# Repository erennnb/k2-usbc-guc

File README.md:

# K2 — USB-C 3.3 V Güç Kartı

USB-C'den aldığı 5 V'u korumalı biçimde 3.3 V'a düşüren, iki katmanlı küçük bir güç kartı.
Yol haritamdaki ilk "üretime hazır" kart: şema, PCB, üretim dosyaları ve doğrulama bu repoda.

> **Durum:** Tasarım tamamlandı · DRC temiz · Gerber hazır · Sipariş verilmedi (simülasyon + inceleme ile doğrulanıyor)

---

## Özellikler

| | |
|---|---|
| **Giriş** | USB-C, yalnız güç (6 pin), 5 V |
| **Çıkış** | 3.3 V, en az 500 mA · ayrıca 5 V çıkış |
| **Koruma** | Polyfuse (aşırı akım) + TVS diyot (gerilim darbesi, ESD) |
| **Gösterge** | 3.3 V hattında güç LED'i |
| **Bağlantı** | 1×3 pin header (5V, 3V3, GND) + 3 test noktası |
| **Kart** | 2 katman, 51.5 × 16 mm |

## Blok diyagram

```mermaid
flowchart LR
    A["USB-C<br/>5 V"] --> B["Polyfuse<br/>0.75 A"]
    B --> C["TVS<br/>SMAJ6.0A"]
    C --> D["AMS1117-3.3<br/>LDO"]
    D --> E["3.3 V çıkış<br/>J2 · TP2"]
    C --> F["5 V çıkış<br/>J2 · TP1"]
    D --> G["Güç LED'i"]
    A -. "CC1 / CC2" .-> H["2 × 5.1 kΩ<br/>pull-down"]
```

## Şema

[Şemanın PDF hâli](docs/k2-schematic.pdf)

## PCB

| Üst yüz | Alt yüz |
|---|---|
|  |  |

---

## Malzeme listesi (BOM)

| Ref | Parça | LCSC | JLCPCB | Not |
|---|---|---|---|---|
| J1 | SHOU HAN TYPE-C 6P | C456012 | Extended | Yalnız güç, SMD, dik açılı, THT tırnaklı |
| R1, R2 | 5.1 kΩ %1 0805 | C27834 | Basic | CC1 / CC2 pull-down |
| F1 | FSMD075-1206R | C5144563 | Extended | Polyfuse, I_hold 0.75 A, V_max 8 V |
| D1 | SMAJ6.0A | C83329 | Extended | TVS, tek yönlü, V_R 6.0 V, V_C 10.3 V |
| C1 | 10 µF 25 V X5R 0805 | C15850 | Basic | LDO giriş kondansatörü |
| U1 | AMS1117-3.3 (SOT-223) | C6186 | Basic | 3.3 V LDO |
| C2 | 22 µF 10 V tantal (B kılıf) | C7198 | Extended | LDO çıkış kondansatörü, ESR 2.4 Ω |
| D2 | Kırmızı LED 0805 | C84256 | Basic | V_F 1.6–2.6 V |
| R3 | 1 kΩ %1 0805 | C17513 | Basic | LED akım direnci |
| J2 | 1×3 pin header, 2.54 mm | — | — | Dik, THT |
| TP1–TP3 | Test noktası | — | — | PCB pad'i |

---

## Tasarım kararları ve hesaplar

### Regülatör: neden AMS1117, neden AP2112K değil?

5 V → 3.3 V, 500 mA'de regülatörde harcanan güç:

**P = (5 − 3.3) × 0.5 = 0.85 W**

| | AMS1117-3.3 (SOT-223) | AP2112K-3.3 (SOT-23-5) |
|---|---|---|
| Dropout (maks.) | 1.3 V | 0.4 V |
| θJA | 90 °C/W | 184 °C/W |
| ΔT (0.85 W) | ≈ 77 °C | ≈ 156 °C |
| Tj (25 °C ortam) | ≈ 102 °C ✓ | ≈ 181 °C ✗ |

AP2112K dropout'ta çok daha iyi, ama küçük kılıfı 0.85 W'ı atamıyor: 25 °C ortamda en fazla ~320 mA verebilir.
500 mA gereksinimi için **AMS1117** seçildi. Bedeli: dropout payı az ve termal bakır alan şart.

### Termal hesap: Tj = Ta + P × θJA

| Ortam (Ta) | Tj | 125 °C sınırı |
|---|---|---|
| 25 °C | 101,5 °C | 125 °C sınırının altında |
| 40 °C | 116,5 °C | Sınıra yakın, pay az |
| 60 °C | 136,5 °C | 125 °C’yi aşıyor |

<!-- TODO: Hangi sıcaklıkta sınır aşılıyor, o durumda ne yapılmalı? -->

### Koruma

- **Polyfuse (0.75 A):** I_hold, 500 mA'lik yük akımının üstünde olmalı; sıcaklıkla düşen I_hold ve açılıştaki ani akımlar için ~%50 pay bırakıldı. V_max 8 V, darbe sırasında hattın kısa süre 5 V'u aşmasına karşı pay.
- **TVS (SMAJ6.0A):** USB-C'de VBUS 5.5 V'a kadar çıkabildiği için V_R ≥ 5.5 V olmalı → 5.0A yerine 6.0A. V_C = 10.3 V, AMS1117'nin maksimum giriş geriliminin altında. Hat hiç negatife düşmediği için **tek yönlü**; negatif darbeleri de ~−0.7 V'ta keser.

### Kondansatörler

- **C1 = 10 µF seramik:** AMS1117 datasheet'inin önerdiği değer. USB, cihazın VBUS hattındaki kapasiteyi 10 µF ile sınırlar (açılıştaki ani akım için). 25 V değer, DC bias kaybını azaltmak için.
- **C2 = 22 µF tantal:** AMS1117 kararlı çalışmak için çıkış kondansatöründe belirli bir ESR ister; çok düşük ESR'li seramik kondansatörle salınıma girebilir.

### CC dirençleri

<!-- TODO: 2–3 cümleyle kendi cümlelerinle yaz:
     1) Bu dirençler ne işe yarıyor?
     2) İkisini neden tek dirençle birleştiremeyiz?
     3) Hiç direnç koymazsan ne olur? -->

### Güç LED'i

R = (3.3 − V_F) / I → (3.3 − 2.0) / 1 kΩ ≈ **1.3 mA**.
Yeşil LED'in V_F değeri (2.6–3.1 V) 3.3 V'a çok yakın olduğu için kırmızı seçildi.

### PCB yerleşimi

- **İz genişlikleri:** güç hatları 0.5 mm (500 mA'de 30 mm'lik izde ≈ 15 mV düşüm), sinyal hatları 0.25 mm.
- **Alt katman kesintisiz GND düzlemi.** SMD GND pad'leri kendi via'larıyla düzleme iner.
- **USB-C'nin iki VBUS pad'i** (A9, B9) arada CC pad'leri olduğu için alt katmanda kısa bir izle birleştirildi.
- **TVS'nin GND via'sı** pad'in dibinde: darbe akımı en kısa yoldan düzleme gitsin.
- **AMS1117'nin tab'ı** (+3V3) üst katmanda katı bağlantılı bir bakır alana bağlı: termal soğutucu.
- **USB-C** kart kenarından taşacak şekilde yerleştirildi; fiş tam otursun.

---

## Doğrulama

| Kontrol | Sonuç |
|---|---|
| ERC (şema) | 0 hata |
| DRC (PCB) | 0 hata, 0 uyarı |
| Şema ↔ PCB paritesi | 0 fark |
| Bağlantısız öğe | 0 |
| İstisnalar | 2 — J1'in silkscreen'i kart kenarında kırpılıyor (konnektör bilerek kenardan taşıyor) |
| JLCPCB önizlemesi | 2 katman, 16 × 51.5 mm, sorun yok |

### LTspice: yük basamağı (0 → 500 mA)

Yük basamağında çıkış kısa süreliğine 2,8 V’a düşüyor, 3,7 V’a fırlıyor ve yaklaşık 10 µs içinde 3,3 V’a oturuyor.

<!-- TODO: Çıkış ne kadar düştü, ne kadar sürede toparlandı? (Model: LT1117-3.3) -->

---

## Üretim

- Gerber + delik dosyaları: [`gerber.zip`](gerber.zip)
- JLCPCB önizlemesi: 2 katman, 51.5 × 16 mm
- Tahmini maliyet (5 adet, 17 Kasım 2026): kart $4.10 + kargo ≈ $26

---

## Öğrendiklerim

- **Özet bilgiler çelişebilir, geçerli olan datasheet.** USB-C konnektörü için JLCPCB 3 A, LCSC 5 A diyordu.
- **Çok versiyonlu datasheet'lerde doğru tabloya bak.** AP2112K'nın dropout'unu ilk okumada 2.5 V'luk versiyonun tablosundan okudum.
- **3.3 V'ta yeşil, mavi ve beyaz LED sorunlu**: V_F'leri 3 V civarında.
- **İndirilen footprint'lerde pad numaralarını sembolle karşılaştır.** EasyEDA kılıf tırnaklarına `7` demişti, KiCad sembolü `SH` bekliyordu.
- **3D görünüm hata yakalar.** İndirilen 3D model 180° ters ve kaymıştı; footprint ise doğruydu.
- **AI'ın verdiği pin numarasını doğrula.** Kılıf pininin numarası bana `S1` olarak söylendi, gerçekte `SH`'ydi; KiCad'in hata mesajı yakaladı.

## v2 için notlar

- [ ] U1'i 180° döndür: küçük pinler girişe, tab çıkışa baksın. +5V ve +3V3 hatları U1'in etrafından dolaşmasın.
- [ ] Montaj delikleri ekle.
- [ ] Termal alanı büyüt; alt katmana termal via'lı bir +3V3 adacığı düşün.
- [ ] Daha düşük dropout'lu ve 500 mA'i kaldıran bir LDO araştır.

---

## Repo yapısı

```
k2-usbc-guc/
├── k2-usbc-guc.kicad_pro / .kicad_sch / .kicad_pcb
├── lib/            USB-C footprint, sembol ve 3D model (easyeda2kicad, C456012)
├── fp-lib-table    proje footprint kütüphanesi
├── gerber/         üretim dosyaları
├── gerber.zip
└── docs/           görseller, şema PDF'i
```

KiCad 10 ile tasarlandı.# K2 — USB-C 3.3 V Güç Kartı

USB-C'den aldığı 5 V'u korumalı biçimde 3.3 V'a düşüren, iki katmanlı küçük bir güç kartı.
Yol haritamdaki ilk "üretime hazır" kart: şema, PCB, üretim dosyaları ve doğrulama bu repoda.

> **Durum:** Tasarım tamamlandı · DRC temiz · Gerber hazır · Sipariş verilmedi (simülasyon + inceleme ile doğrulanıyor)

---

## Özellikler

| | |
|---|---|
| **Giriş** | USB-C, yalnız güç (6 pin), 5 V |
| **Çıkış** | 3.3 V, en az 500 mA · ayrıca 5 V çıkış |
| **Koruma** | Polyfuse (aşırı akım) + TVS diyot (gerilim darbesi, ESD) |
| **Gösterge** | 3.3 V hattında güç LED'i |
| **Bağlantı** | 1×3 pin header (5V, 3V3, GND) + 3 test noktası |
| **Kart** | 2 katman, 51.5 × 16 mm |

## Blok diyagram

```mermaid
flowchart LR
    A["USB-C<br/>5 V"] --> B["Polyfuse<br/>0.75 A"]
    B --> C["TVS<br/>SMAJ6.0A"]
    C --> D["AMS1117-3.3<br/>LDO"]
    D --> E["3.3 V çıkış<br/>J2 · TP2"]
    C --> F["5 V çıkış<br/>J2 · TP1"]
    D --> G["Güç LED'i"]
    A -. "CC1 / CC2" .-> H["2 × 5.1 kΩ<br/>pull-down"]
```

## Şema

[Şemanın PDF hâli](docs/k2-schematic.pdf)

## PCB

| Üst yüz | Alt yüz |
|---|---|
|  |  |

---

## Malzeme listesi (BOM)

| Ref | Parça | LCSC | JLCPCB | Not |
|---|---|---|---|---|
| J1 | SHOU HAN TYPE-C 6P | C456012 | Extended | Yalnız güç, SMD, dik açılı, THT tırnaklı |
| R1, R2 | 5.1 kΩ %1 0805 | C27834 | Basic | CC1 / CC2 pull-down |
| F1 | FSMD075-1206R | C5144563 | Extended | Polyfuse, I_hold 0.75 A, V_max 8 V |
| D1 | SMAJ6.0A | C83329 | Extended | TVS, tek yönlü, V_R 6.0 V, V_C 10.3 V |
| C1 | 10 µF 25 V X5R 0805 | C15850 | Basic | LDO giriş kondansatörü |
| U1 | AMS1117-3.3 (SOT-223) | C6186 | Basic | 3.3 V LDO |
| C2 | 22 µF 10 V tantal (B kılıf) | C7198 | Extended | LDO çıkış kondansatörü, ESR 2.4 Ω |
| D2 | Kırmızı LED 0805 | C84256 | Basic | V_F 1.6–2.6 V |
| R3 | 1 kΩ %1 0805 | C17513 | Basic | LED akım direnci |
| J2 | 1×3 pin header, 2.54 mm | — | — | Dik, THT |
| TP1–TP3 | Test noktası | — | — | PCB pad'i |

---

## Tasarım kararları ve hesaplar

### Regülatör: neden AMS1117, neden AP2112K değil?

5 V → 3.3 V, 500 mA'de regülatörde harcanan güç:

**P = (5 − 3.3) × 0.5 = 0.85 W**

| | AMS1117-3.3 (SOT-223) | AP2112K-3.3 (SOT-23-5) |
|---|---|---|
| Dropout (maks.) | 1.3 V | 0.4 V |
| θJA | 90 °C/W | 184 °C/W |
| ΔT (0.85 W) | ≈ 77 °C | ≈ 156 °C |
| Tj (25 °C ortam) | ≈ 102 °C ✓ | ≈ 181 °C ✗ |

AP2112K dropout'ta çok daha iyi, ama küçük kılıfı 0.85 W'ı atamıyor: 25 °C ortamda en fazla ~320 mA verebilir.
500 mA gereksinimi için **AMS1117** seçildi. Bedeli: dropout payı az ve termal bakır alan şart.

### Termal hesap: Tj = Ta + P × θJA

| Ortam (Ta) | Tj | 125 °C sınırı |
|---|---|---|
| 25 °C | <!-- TODO --> | <!-- TODO --> |
| 40 °C | <!-- TODO --> | <!-- TODO --> |
| 60 °C | <!-- TODO --> | <!-- TODO --> |

<!-- TODO: Hangi sıcaklıkta sınır aşılıyor, o durumda ne yapılmalı? -->

### Koruma

- **Polyfuse (0.75 A):** I_hold, 500 mA'lik yük akımının üstünde olmalı; sıcaklıkla düşen I_hold ve açılıştaki ani akımlar için ~%50 pay bırakıldı. V_max 8 V, darbe sırasında hattın kısa süre 5 V'u aşmasına karşı pay.
- **TVS (SMAJ6.0A):** USB-C'de VBUS 5.5 V'a kadar çıkabildiği için V_R ≥ 5.5 V olmalı → 5.0A yerine 6.0A. V_C = 10.3 V, AMS1117'nin maksimum giriş geriliminin altında. Hat hiç negatife düşmediği için **tek yönlü**; negatif darbeleri de ~−0.7 V'ta keser.

### Kondansatörler

- **C1 = 10 µF seramik:** AMS1117 datasheet'inin önerdiği değer. USB, cihazın VBUS hattındaki kapasiteyi 10 µF ile sınırlar (açılıştaki ani akım için). 25 V değer, DC bias kaybını azaltmak için.
- **C2 = 22 µF tantal:** AMS1117 kararlı çalışmak için çıkış kondansatöründe belirli bir ESR ister; çok düşük ESR'li seramik kondansatörle salınıma girebilir.

### CC dirençleri

<!-- TODO: 2–3 cümleyle kendi cümlelerinle yaz:
     1) Bu dirençler ne işe yarıyor?
     2) İkisini neden tek dirençle birleştiremeyiz?
     3) Hiç direnç koymazsan ne olur? -->

### Güç LED'i

R = (3.3 − V_F) / I → (3.3 − 2.0) / 1 kΩ ≈ **1.3 mA**.
Yeşil LED'in V_F değeri (2.6–3.1 V) 3.3 V'a çok yakın olduğu için kırmızı seçildi.

### PCB yerleşimi

- **İz genişlikleri:** güç hatları 0.5 mm (500 mA'de 30 mm'lik izde ≈ 15 mV düşüm), sinyal hatları 0.25 mm.
- **Alt katman kesintisiz GND düzlemi.** SMD GND pad'leri kendi via'larıyla düzleme iner.
- **USB-C'nin iki VBUS pad'i** (A9, B9) arada CC pad'leri olduğu için alt katmanda kısa bir izle birleştirildi.
- **TVS'nin GND via'sı** pad'in dibinde: darbe akımı en kısa yoldan düzleme gitsin.
- **AMS1117'nin tab'ı** (+3V3) üst katmanda katı bağlantılı bir bakır alana bağlı: termal soğutucu.
- **USB-C** kart kenarından taşacak şekilde yerleştirildi; fiş tam otursun.

---

## Doğrulama

| Kontrol | Sonuç |
|---|---|
| ERC (şema) | 0 hata |
| DRC (PCB) | 0 hata, 0 uyarı |
| Şema ↔ PCB paritesi | 0 fark |
| Bağlantısız öğe | 0 |
| İstisnalar | 2 — J1'in silkscreen'i kart kenarında kırpılıyor (konnektör bilerek kenardan taşıyor) |
| JLCPCB önizlemesi | 2 katman, 16 × 51.5 mm, sorun yok |

### LTspice: yük basamağı (0 → 500 mA)

<!-- TODO: Çıkış ne kadar düştü, ne kadar sürede toparlandı? (Model: LT1117-3.3) -->

---

## Üretim

- Gerber + delik dosyaları: [`gerber.zip`](gerber.zip)
- JLCPCB önizlemesi: 2 katman, 51.5 × 16 mm
- Tahmini maliyet (5 adet, 17 Kasım 2026): kart $4.10 + kargo ≈ $26

---

## Öğrendiklerim

- **Özet bilgiler çelişebilir, geçerli olan datasheet.** USB-C konnektörü için JLCPCB 3 A, LCSC 5 A diyordu.
- **Çok versiyonlu datasheet'lerde doğru tabloya bak.** AP2112K'nın dropout'unu ilk okumada 2.5 V'luk versiyonun tablosundan okudum.
- **3.3 V'ta yeşil, mavi ve beyaz LED sorunlu**: V_F'leri 3 V civarında.
- **İndirilen footprint'lerde pad numaralarını sembolle karşılaştır.** EasyEDA kılıf tırnaklarına `7` demişti, KiCad sembolü `SH` bekliyordu.
- **3D görünüm hata yakalar.** İndirilen 3D model 180° ters ve kaymıştı; footprint ise doğruydu.
- **AI'ın verdiği pin numarasını doğrula.** Kılıf pininin numarası bana `S1` olarak söylendi, gerçekte `SH`'ydi; KiCad'in hata mesajı yakaladı.

## v2 için notlar

- [ ] U1'i 180° döndür: küçük pinler girişe, tab çıkışa baksın. +5V ve +3V3 hatları U1'in etrafından dolaşmasın.
- [ ] Montaj delikleri ekle.
- [ ] Termal alanı büyüt; alt katmana termal via'lı bir +3V3 adacığı düşün.
- [ ] Daha düşük dropout'lu ve 500 mA'i kaldıran bir LDO araştır.

---

## Repo yapısı

```
k2-usbc-guc/
├── k2-usbc-guc.kicad_pro / .kicad_sch / .kicad_pcb
├── lib/            USB-C footprint, sembol ve 3D model (easyeda2kicad, C456012)
├── fp-lib-table    proje footprint kütüphanesi
├── gerber/         üretim dosyaları
├── gerber.zip
└── docs/           görseller, şema PDF'i
```

KiCad 10 ile tasarlandı.

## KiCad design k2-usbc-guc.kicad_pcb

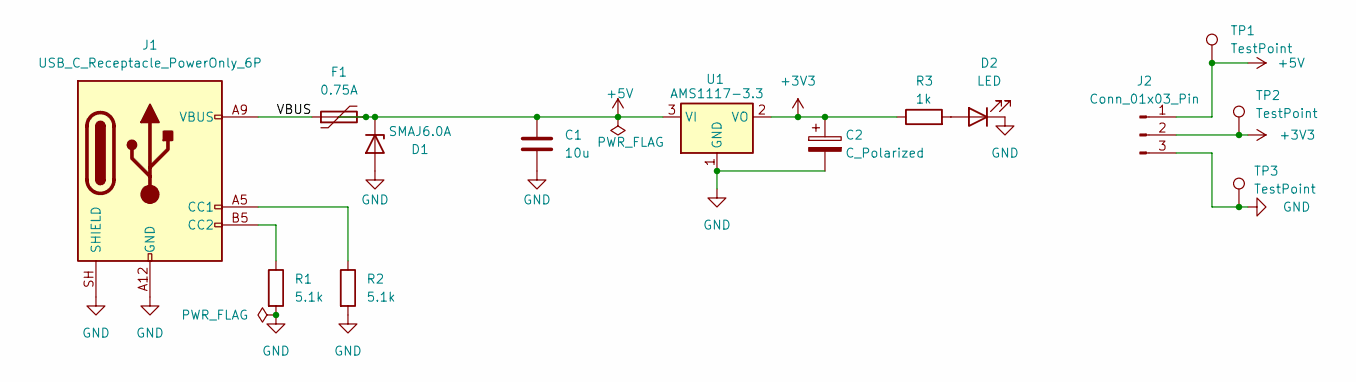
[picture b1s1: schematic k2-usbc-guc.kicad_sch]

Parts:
C1: 10u; C_0805_2012Metric
C2: C_Polarized; CP_EIA-3528-21_Kemet-B
D1: SMAJ6.0A; D_SMA
D2: LED; LED_0805_2012Metric
F1: 0.75A; Fuse_1206_3216Metric
J1: USB_C_Receptacle_PowerOnly_6P; TYPE-C-SMD_TYPE-C-6P_1
J2: Conn_01x03_Pin; PinHeader_1x03_P2.54mm_Vertical
R1, R2: 5.1k; R_0805_2012Metric
R3: 1k; R_0805_2012Metric
TP1, TP2, TP3: TestPoint; TestPoint_Pad_D1.5mm
U1: AMS1117-3.3; SOT-223-3_TabPin2

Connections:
+3V3: C2.1, J2.2, R3.1, TP2.1 (1_1), U1.2 (VO)
+5V: C1.1, D1.1 (K), F1.2, J2.1, TP1.1 (1_1), U1.3 (VI)
/VBUS: F1.1, J1.A9 (VBUS), J1.B9 (VBUS)
GND: C1.2, C2.2, D1.2 (A), D2.1 (K), J1.A12 (GND), J1.B12 (GND), J1.SH (SHIELD), J2.3, R1.2, R2.2, TP3.1 (1_1), U1.1 (GND)
unnamed: D2.2 (A), R3.2
unnamed: J1.A5 (CC1), R2.1
unnamed: J1.B5 (CC2), R1.1

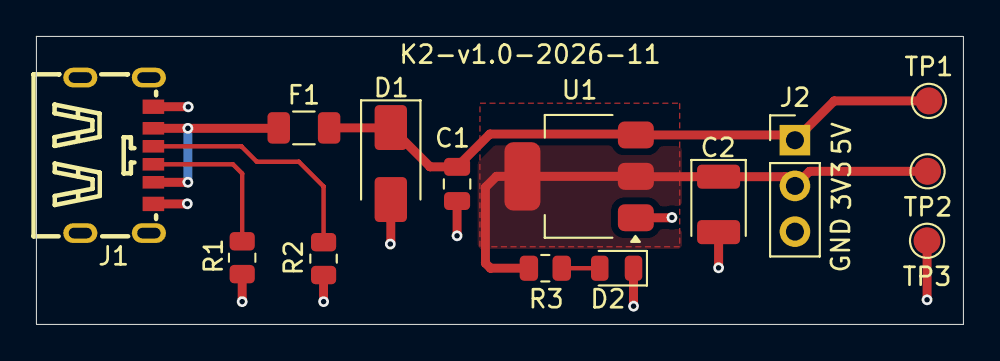
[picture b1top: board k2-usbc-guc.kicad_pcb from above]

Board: 2 copper layers, 51.5 x 16.0 mm, 14 parts (0 on the bottom side), 7 nets.
